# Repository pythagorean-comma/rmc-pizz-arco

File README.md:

# rmc-pizz-arco

A six-channel phase-switching preamp for RMC pizz/arco piezo pickups, generated
from source rather than drawn by hand.

Each of the six saddles of a viola da gamba bridge holds **two** piezo elements.
This board sums each pair into a single high-impedance output that looks like a
piezo to an RMC Poly-Drive II, and lets a toggle flip the relative polarity of
the two: in phase for picking, out of phase for bowing. It is six copies of
one channel of RMC's own schematic
([`docs/Pizz-Arco-Switching-260729.png`](docs/Pizz-Arco-Switching-260729.png)),
plus the supply and switching that drawing leaves open.

The switch exists because the saddle is quasi-omniplanar but blind to one
direction of string rotation, so no static circuit can give both an omniplanar
response and a symmetric attack. [`DESIGN.md`](DESIGN.md) opens with RMC's own
account of it.

The bridge these pickups sit in is a separate project:
<https://github.com/pythagorean-comma/violet-bridge>.

## Everything is generated

`design.py` is the single source of truth for the circuit. `gen_sch.py` draws
the schematic from it, `gen_pcb.py` places and routes the board from it,
`gen_sim.py` draws a simulation sheet from it, and `verify.py` reads KiCad's own
netlist back and compares it net by net.

```bash
./build.sh
```

That regenerates schematic *and* board, runs ERC, checks both against
`design.py`, runs DRC, and writes `fab/rmc-pizz-arco-pcbway.zip`, but **only
when DRC is clean**, so a board with known faults cannot reach a fab by
accident.

> **Anything changed in the KiCad GUI is destroyed by the next build.** Use the
> editor to inspect, measure and try things out; changes that should survive
> belong in the generator.

## Simulating it

`./build.sh` also writes `rmc-pizz-arco/rmc-pizz-arco-sim.kicad_sch`. Open it in
KiCad and press Simulate; KiCad ships ngspice, so there is nothing to install.
It tests the board's central claim — that the toggle flips polarity without
changing level — and the low-frequency behaviour of the two piezo elements
summing, which is where the surprises were. One file is needed and is not in
this repository: TI's OPAx191 macromodel, from
<https://www.ti.com/lit/zip/SBOMA30>, because their licence grants use but not
redistribution. [`gen_sim.py`](gen_sim.py) says where to put it, and
[`DESIGN.md`](DESIGN.md) says what the analyses found and what a failure would
have looked like.

## Requirements

**KiCad 10.x.** Install with `brew install --cask kicad`, or from
<https://www.kicad.org/download/>. The file formats written are version
specific: KiCad 9 will not open the generated schematic.

**No Python packages.** There is no virtual environment and no
`requirements.txt`, because there is nothing to install: the generators are
pure standard library. The one exception is `pcbnew`, which ships inside KiCad,
so `build.sh` runs `gen_pcb.py` under KiCad's own bundled interpreter and
everything else under `python3`. Set `PYTHON` to override which one.

`kicad.py` finds the installation. It checks `$KICAD_APP`, then
`/Applications/KiCad/KiCad.app`, then `~/Applications/KiCad/KiCad.app`, then
`kicad-cli` on `PATH`. If yours lives somewhere else:

```bash
export KICAD_APP=/path/to/KiCad.app
```

Run `python3 kicad.py` to see what it found.

## Where to read next

| | |
| --- | --- |
| [`DESIGN.md`](DESIGN.md) | What the circuit does and why, what must not be got wrong when wiring it, how the board came out, and what is still open with RMC. **Start here.** |
| [`fab/ORDER.md`](fab/ORDER.md) | How to order it, including the four requirements that are invisible in the gerbers and the BOM. |
| [`ENCLOSURE.md`](ENCLOSURE.md) | The tail-mounted housing study. Mounting and the loom are settled in principle; the box is not yet designed. |
| [`docs/`](docs) | RMC's own schematic, and the correspondence: what was sent to them and the memo written before acting on their review. Records, not specifications — where they and `DESIGN.md` differ, `DESIGN.md` is right. |

## Status

Placed, routed and **DRC-clean** at 77.2 × 82.4 mm: 47 nets, 233 pin
connections, 80 placements, 0 violations, 0 unconnected items. Nothing has been
fabricated.

This is **rev D**, which is RMC's rev.3: it answers their layout review of
2026-08-01 and its addendum — the V− plane moved onto In2, the four bypass
capacitors became ten, every design rule widened, the all-pass feedback pair
moved up against the op-amp, and the buffer's 1 kΩ deleted. Three questions are
still awaiting reply and one of them blocks ordering; all are listed in
[`DESIGN.md`](DESIGN.md).

**Simulated, and no change to the board follows from it.** The polarity flip and
the 34 kHz corner check out; the level match holds to about 3 kHz and reaches
1.5 dB at 20 kHz; the summing capacitor turns out to be right for a reason
nobody had written down. The one result worth acting on is a question rather
than a fix — the Poly-Drive II's input impedance, which sets the bass response
and which only RMC can supply.

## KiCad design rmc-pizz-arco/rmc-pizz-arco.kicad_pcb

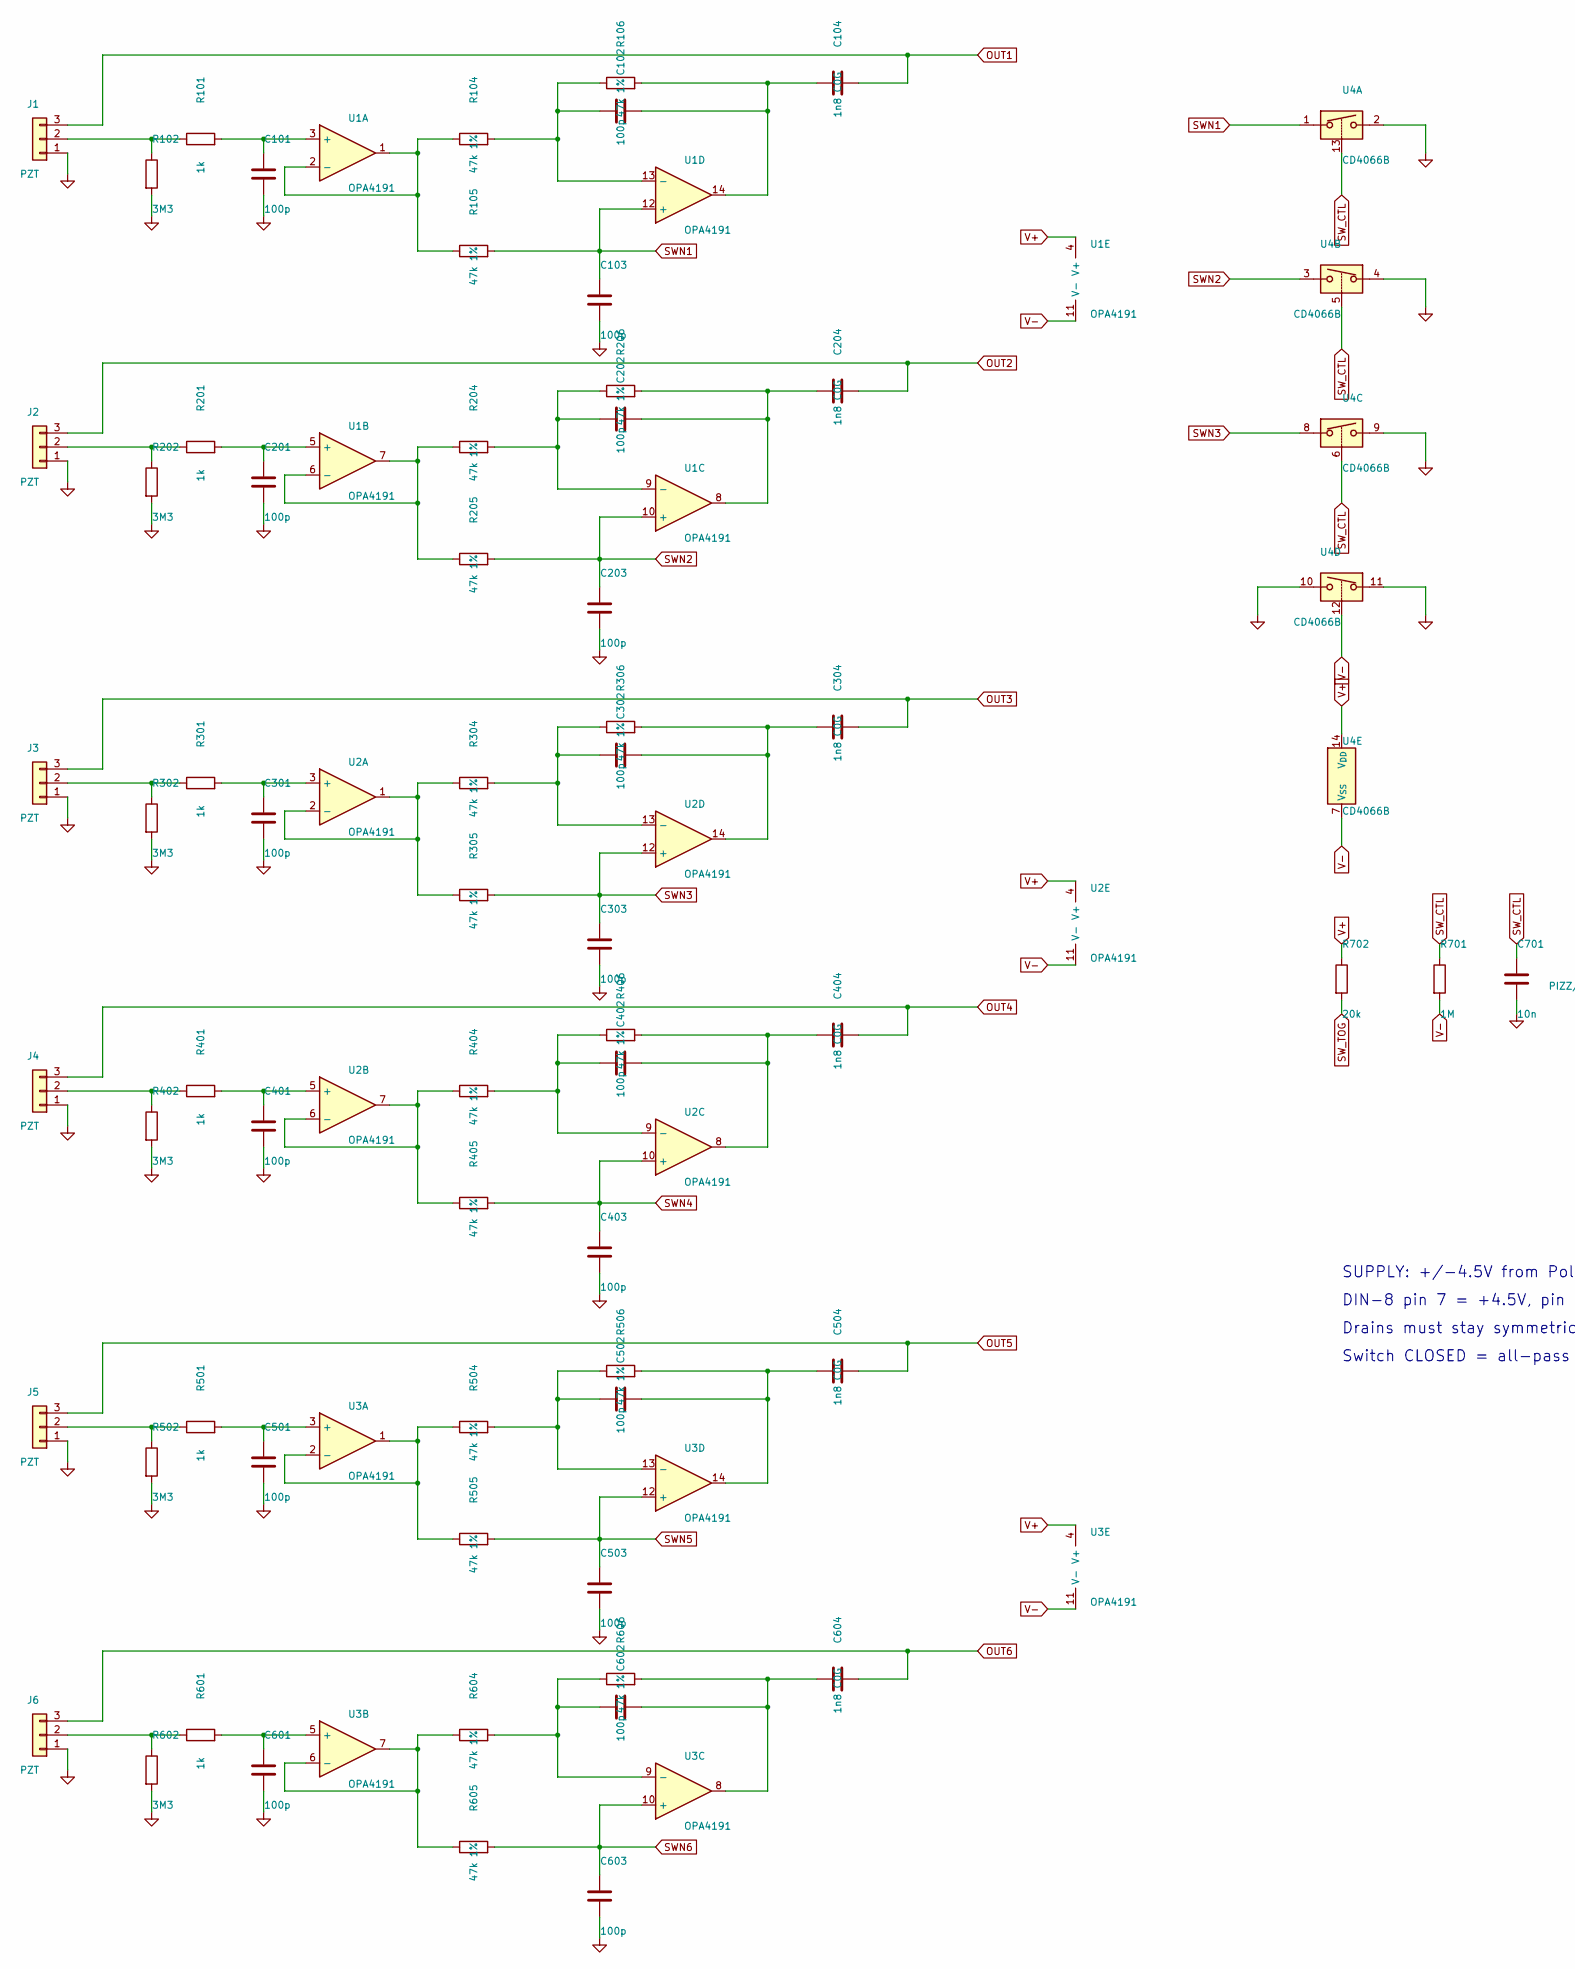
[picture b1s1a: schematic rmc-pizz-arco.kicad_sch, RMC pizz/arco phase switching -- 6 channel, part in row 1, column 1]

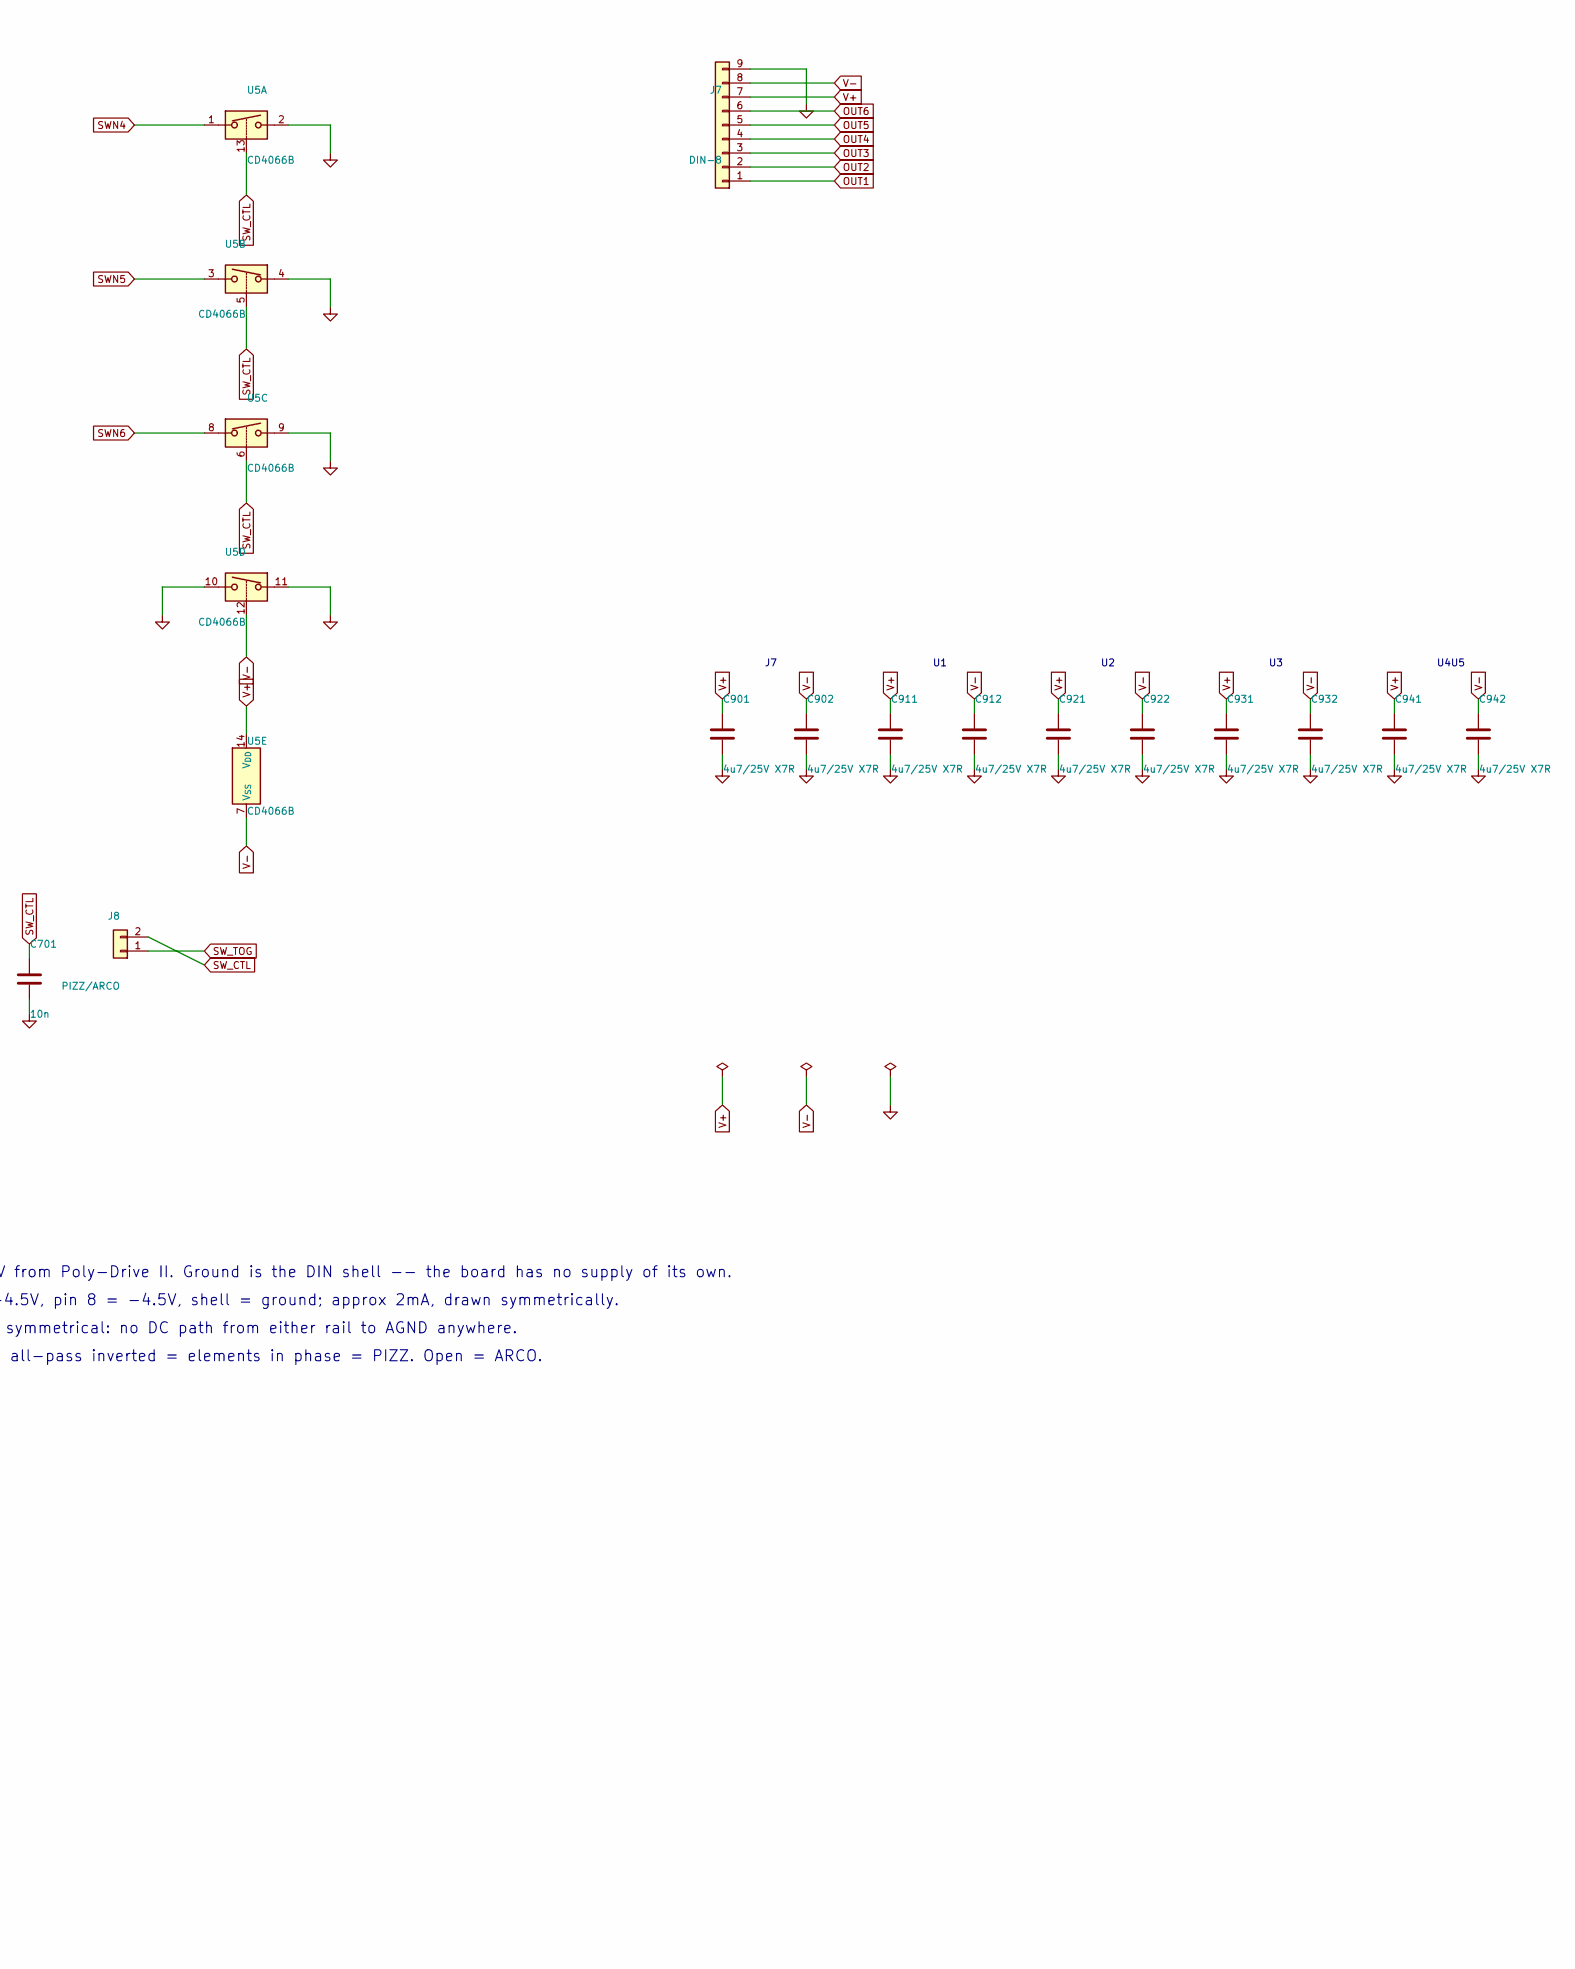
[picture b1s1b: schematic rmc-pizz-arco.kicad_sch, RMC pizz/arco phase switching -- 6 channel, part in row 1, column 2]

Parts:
C101, C102, C103, C201, C202, C203, C301, C302, C303, C401, C402, C403, C501, C502, C503, C601, C602, C603: 100p; C_1206_3216Metric
C104, C204, C304, C404, C504, C604: 1n8 C0G; C_1206_3216Metric
C701: 10n; C_1206_3216Metric
C901, C902, C911, C912, C921, C922, C931, C932, C941, C942: 4u7/25V X7R; C_1206_3216Metric
J1, J2, J3, J4, J5, J6: PZT; PinHeader_1x03_P2.54mm_Vertical
J7: DIN-8; PinHeader_1x09_P2.54mm_Vertical
J8: PIZZ/ARCO; PinHeader_1x02_P2.54mm_Vertical
R101, R201, R301, R401, R501, R601: 1k; R_1206_3216Metric
R102, R202, R302, R402, R502, R602: 3M3; R_1206_3216Metric
R104, R105, R106, R204, R205, R206, R304, R305, R306, R404, R405, R406, R504, R505, R506, R604, R605, R606: 47k 1%; R_1206_3216Metric
R701: 1M; R_1206_3216Metric
R702: 20k; R_1206_3216Metric
U1, U2, U3: OPA4191; SOIC-14_3.9x8.7mm_P1.27mm
U4, U5: CD4066B; SO-14_3.9x8.65mm_P1.27mm

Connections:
AGND: C101.2, C103.2, C201.2, C203.2, C301.2, C303.2, C401.2, C403.2, C501.2, C503.2, C601.2, C603.2, C701.2, C901.2, C902.2, C911.2, C912.2, C921.2, C922.2, C931.2, C932.2, C941.2, C942.2, J1.1, J2.1, J3.1, J4.1, J5.1, J6.1, J7.9, R102.2, R202.2, R302.2, R402.2, R502.2, R602.2, U4.2, U4.4, U4.9, U4.10, U4.11, U5.2, U5.4, U5.9, U5.10, U5.11
APN1: C102.1, R104.2, R106.1, U1.13 (-)
APN2: C202.1, R204.2, R206.1, U1.9 (-)
APN3: C302.1, R304.2, R306.1, U2.13 (-)
APN4: C402.1, R404.2, R406.1, U2.9 (-)
APN5: C502.1, R504.2, R506.1, U3.13 (-)
APN6: C602.1, R604.2, R606.1, U3.9 (-)
APOUT1: C102.2, C104.1, R106.2, U1.14
APOUT2: C202.2, C204.1, R206.2, U1.8
APOUT3: C302.2, C304.1, R306.2, U2.14
APOUT4: C402.2, C404.1, R406.2, U2.8
APOUT5: C502.2, C504.1, R506.2, U3.14
APOUT6: C602.2, C604.1, R606.2, U3.8
BUFIN1: C101.1, R101.2, U1.3 (+)
BUFIN2: C201.1, R201.2, U1.5 (+)
BUFIN3: C301.1, R301.2, U2.3 (+)
BUFIN4: C401.1, R401.2, U2.5 (+)
BUFIN5: C501.1, R501.2, U3.3 (+)
BUFIN6: C601.1, R601.2, U3.5 (+)
BUFOUT1: R104.1, R105.1, U1.1, U1.2 (-)
BUFOUT2: R204.1, R205.1, U1.6 (-), U1.7
BUFOUT3: R304.1, R305.1, U2.1, U2.2 (-)
BUFOUT4: R404.1, R405.1, U2.6 (-), U2.7
BUFOUT5: R504.1, R505.1, U3.1, U3.2 (-)
BUFOUT6: R604.1, R605.1, U3.6 (-), U3.7
IN_W1: J1.2, R101.1, R102.1
IN_W2: J2.2, R201.1, R202.1
IN_W3: J3.2, R301.1, R302.1
IN_W4: J4.2, R401.1, R402.1
IN_W5: J5.2, R501.1, R502.1
IN_W6: J6.2, R601.1, R602.1
OUT1: C104.2, J1.3, J7.1
OUT2: C204.2, J2.3, J7.2
OUT3: C304.2, J3.3, J7.3
OUT4: C404.2, J4.3, J7.4
OUT5: C504.2, J5.3, J7.5
OUT6: C604.2, J6.3, J7.6
SWN1: C103.1, R105.2, U1.12 (+), U4.1
SWN2: C203.1, R205.2, U1.10 (+), U4.3
SWN3: C303.1, R305.2, U2.12 (+), U4.8
SWN4: C403.1, R405.2, U2.10 (+), U5.1
SWN5: C503.1, R505.2, U3.12 (+), U5.3
SWN6: C603.1, R605.2, U3.10 (+), U5.8
SW_CTL: C701.1, J8.2, R701.1, U4.5, U4.6, U4.13, U5.5, U5.6, U5.13
SW_TOG: J8.1, R702.2
V+: C901.1, C911.1, C921.1, C931.1, C941.1, J7.7, R702.1, U1.4 (V+), U2.4 (V+), U3.4 (V+), U4.14 (V_{DD}), U5.14 (V_{DD})
V-: C902.1, C912.1, C922.1, C932.1, C942.1, J7.8, R701.2, U1.11 (V-), U2.11 (V-), U3.11 (V-), U4.7 (V_{SS}), U4.12, U5.7 (V_{SS}), U5.12

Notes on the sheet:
U4U5
SUPPLY: +/-4.5V from Poly-Drive II. Ground is the DIN shell -- the board has no supply of its own.
DIN-8 pin 7 = +4.5V, pin 8 = -4.5V, shell = ground; approx 2mA, drawn symmetrically.
Drains must stay symmetrical: no DC path from either rail to AGND anywhere.
Switch CLOSED = all-pass inverted = elements in phase = PIZZ. Open = ARCO.

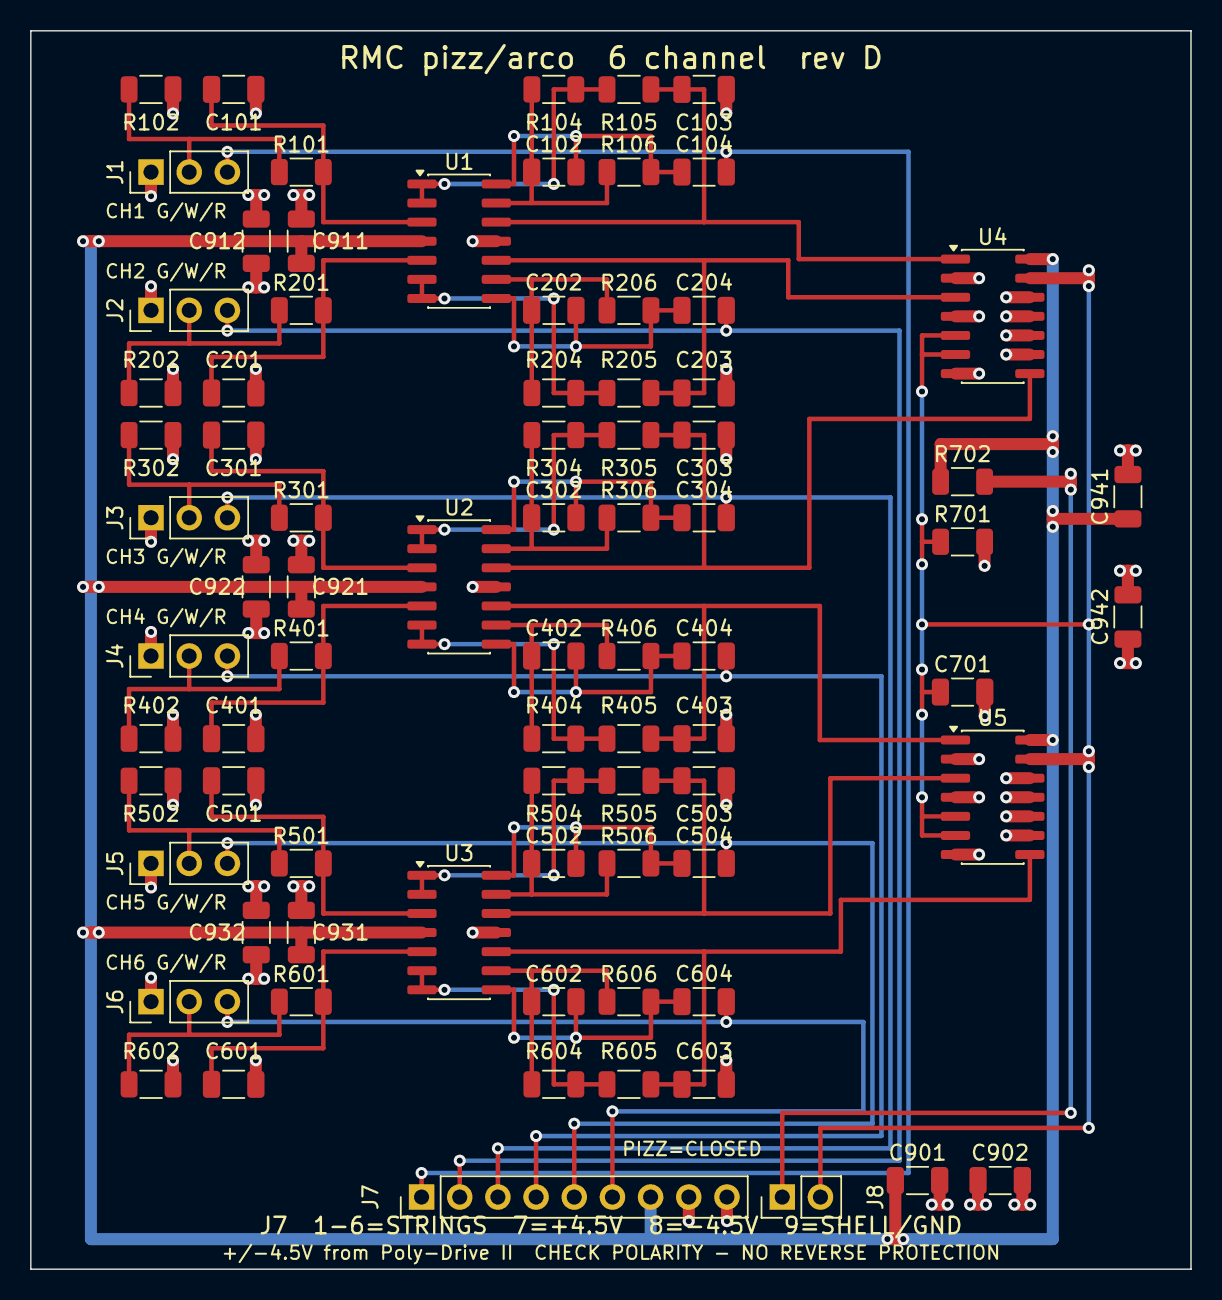
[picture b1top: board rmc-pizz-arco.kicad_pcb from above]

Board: 4 copper layers, 77.2 x 82.4 mm, 80 parts (0 on the bottom side), 47 nets.

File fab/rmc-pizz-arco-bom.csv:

"Reference","Value","Footprint","QUANTITY","Datasheet"
"C101-C103,C201-C203,C301-C303,C401-C403,C501-C503,C601-C603","100p","Capacitor_SMD:C_1206_3216Metric","18","~"
"C104,C204,C304,C404,C504,C604","1n8 C0G","Capacitor_SMD:C_1206_3216Metric","6","~"
"C701","10n","Capacitor_SMD:C_1206_3216Metric","1","~"
"C901,C902,C911,C912,C921,C922,C931,C932,C941,C942","4u7/25V X7R","Capacitor_SMD:C_1206_3216Metric","10","~"
"J1-J6","PZT","Connector_PinHeader_2.54mm:PinHeader_1x03_P2.54mm_Vertical","6","~"
"J7","DIN-8","Connector_PinHeader_2.54mm:PinHeader_1x09_P2.54mm_Vertical","1","~"
"J8","PIZZ/ARCO","Connector_PinHeader_2.54mm:PinHeader_1x02_P2.54mm_Vertical","1","~"
"R101,R201,R301,R401,R501,R601","1k","Resistor_SMD:R_1206_3216Metric","6","~"
"R102,R202,R302,R402,R502,R602","3M3","Resistor_SMD:R_1206_3216Metric","6","~"
"R104-R106,R204-R206,R304-R306,R404-R406,R504-R506,R604-R606","47k 1%","Resistor_SMD:R_1206_3216Metric","18","~"
"R701","1M","Resistor_SMD:R_1206_3216Metric","1","~"
"R702","20k","Resistor_SMD:R_1206_3216Metric","1","~"
"U1-U3","OPA4191","Package_SO:SOIC-14_3.9x8.7mm_P1.27mm","3","https://www.ti.com/lit/ds/symlink/opa4191.pdf"
"U4,U5","CD4066B","Package_SO:SO-14_3.9x8.65mm_P1.27mm","2","https://www.ti.com/lit/ds/symlink/cd4066b.pdf"
